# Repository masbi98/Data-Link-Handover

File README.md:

# Data-Link-Handover
a repository for handover the data link work that was done in my On-Job-Training with Gamuda Technologies.

# ExpressLRS to ArduPilot SITL Real-Time MAVLink Bridge

An ultra-low-latency hardware-in-the-loop (HIL) telemetry bridge developed during On-Job-Training with Gamuda Technologies. This repository provides the pipeline that captures native MAVLink RC override packets from an ExpressLRS (ELRS) receiver and injects them directly into ArduPilot Software-In-The-Loop (SITL) simulations via Mission Planner.

---

## 📌 Project Overview and Architecture

---

## 🛠️ Hardware & Software Stack

- **Transmitter:** Radiomaster T8L
- **Protocol:** ExpressLRS (2.4GHz) configured for MAVLink telemetry output
- **Interface:** FTDI USB-to-UART Serial Converter (`COM6`[or designated com port] `460800` baud)
- **Runtime / Libraries:** Python 3.10+, `pymavlink`
- **Ground Control & Simulation:** Mission Planner, ArduPilot SITL (Multirotor model)

---

## ⚡ Quick Start Guide

### 1. Prerequisites & Installation

Clone the repository and install dependencies:

```bash
git clone [https://github.com/masbi98/Data-Link-Handover.git]
cd Data-Link-Handover
pip install -r requirements.txt
```

### 2. Configure Mission Planner SITL

* Open Mission Planner
* Go to Simulation, choose Multirotor, and select Model. Allow the simulation to fuilly initialize.
* Open the developer utilities by pressing `Ctrl + F`, then click Mavlink.
* Configure the first row of the bridge table:
	- **Type:** `TCP`
	- **Direction:** `Inbound`
	- **Port:** `14556`
	- **Host/Baud:** mirror 14556
	- **Write:** [X] (Checked - critical for pass-through commands)
* Click Go (status much change to Started).

### 3. ArduPilot Parameter tweaks

To prevent false disarms during ground testing or packet jitters:

- Navigate to Config -> Full Parameters List.
- Set `FS_THR_Enable` to `0` (Disables RC throttle failsafe disarm during testing).
- Click Write params.

### 4. Run the Injection Script

Connect your receiver via FTDI and run (Assuming your working directory is already inside this repository):

```bash
python src/sitl_injector.py
```

### 5. Arm & Fly

* Switch to Mission Planner's Flight Data view.
* In the bottom-left **Actions** tab, set the flight mode to **Stabilize** and click **Set Mode**.
* Arm via sticks (Throttle down + Yaw right for 3s) or right-click the map -> **Arm/Disarm** -> **Force Arm**.
* Throttle up on your physical transmitter to control the virtual aircraft.

---

## 🦾 Troubleshooting Reference (System Failures Handled)

* Failed Connection/socket crashes (only one usage of socket address):
	- Causes: Background task ghosting on port `14555` or unclosed TCP relays.
	- Fixes: We routed standard connection ports exclusively onto unused port `14556`. When issues persist, kill tasks by hitting `Ctrl + C` and reboot Mission Planner to refresh system socket configurations.
* SITL parameter collection failures (No Heartbeat received):
	- Causes: Bridge logic crashing due to trying to map standard downloads inside Mission Planner.
	- Fixes: Never touch the main Mission Planer Connect button! Start SITL and connect directly using the internal bridge routing to communicate natively via GCS authentication (source_system=255).
* Uncontrolled random disarming:
	- Causes: Safety timeout failsafes and telemetry drops.
	- Fixes: Disabled internal failsafes (`FS_THR_ENABLE` to `0`) and changed raw signal tracking to asynchronous event-based pass-through triggers. No artificial delays are used, creating immediate, non-blocking control feedback.

---

## 🛠️ Custom PCB Design

This repo includes a custom-designed Printed Circuit Board (PCB) to handle the hardware routing between the ExpressLRS receiver, the microcontroller, and the power delivery systems.\

* **EDA Software:** KICAD
* **Layer Count:** 4 Layer Impedance-controlled stackup
* **Key Features:**
	- Dedicated UART routing for 460,800 baud telemetry lines.
	- Clean power delivery/filtering for the 2.4GHz RF module.
	- Broken-out programming header for flight controller firmware flashing.
* **Manufacturing:** The Zip file that is in the /hardware folder is used, and sent to JLCPCB. file name "Datalink Transceiver PCB files.zip"

---

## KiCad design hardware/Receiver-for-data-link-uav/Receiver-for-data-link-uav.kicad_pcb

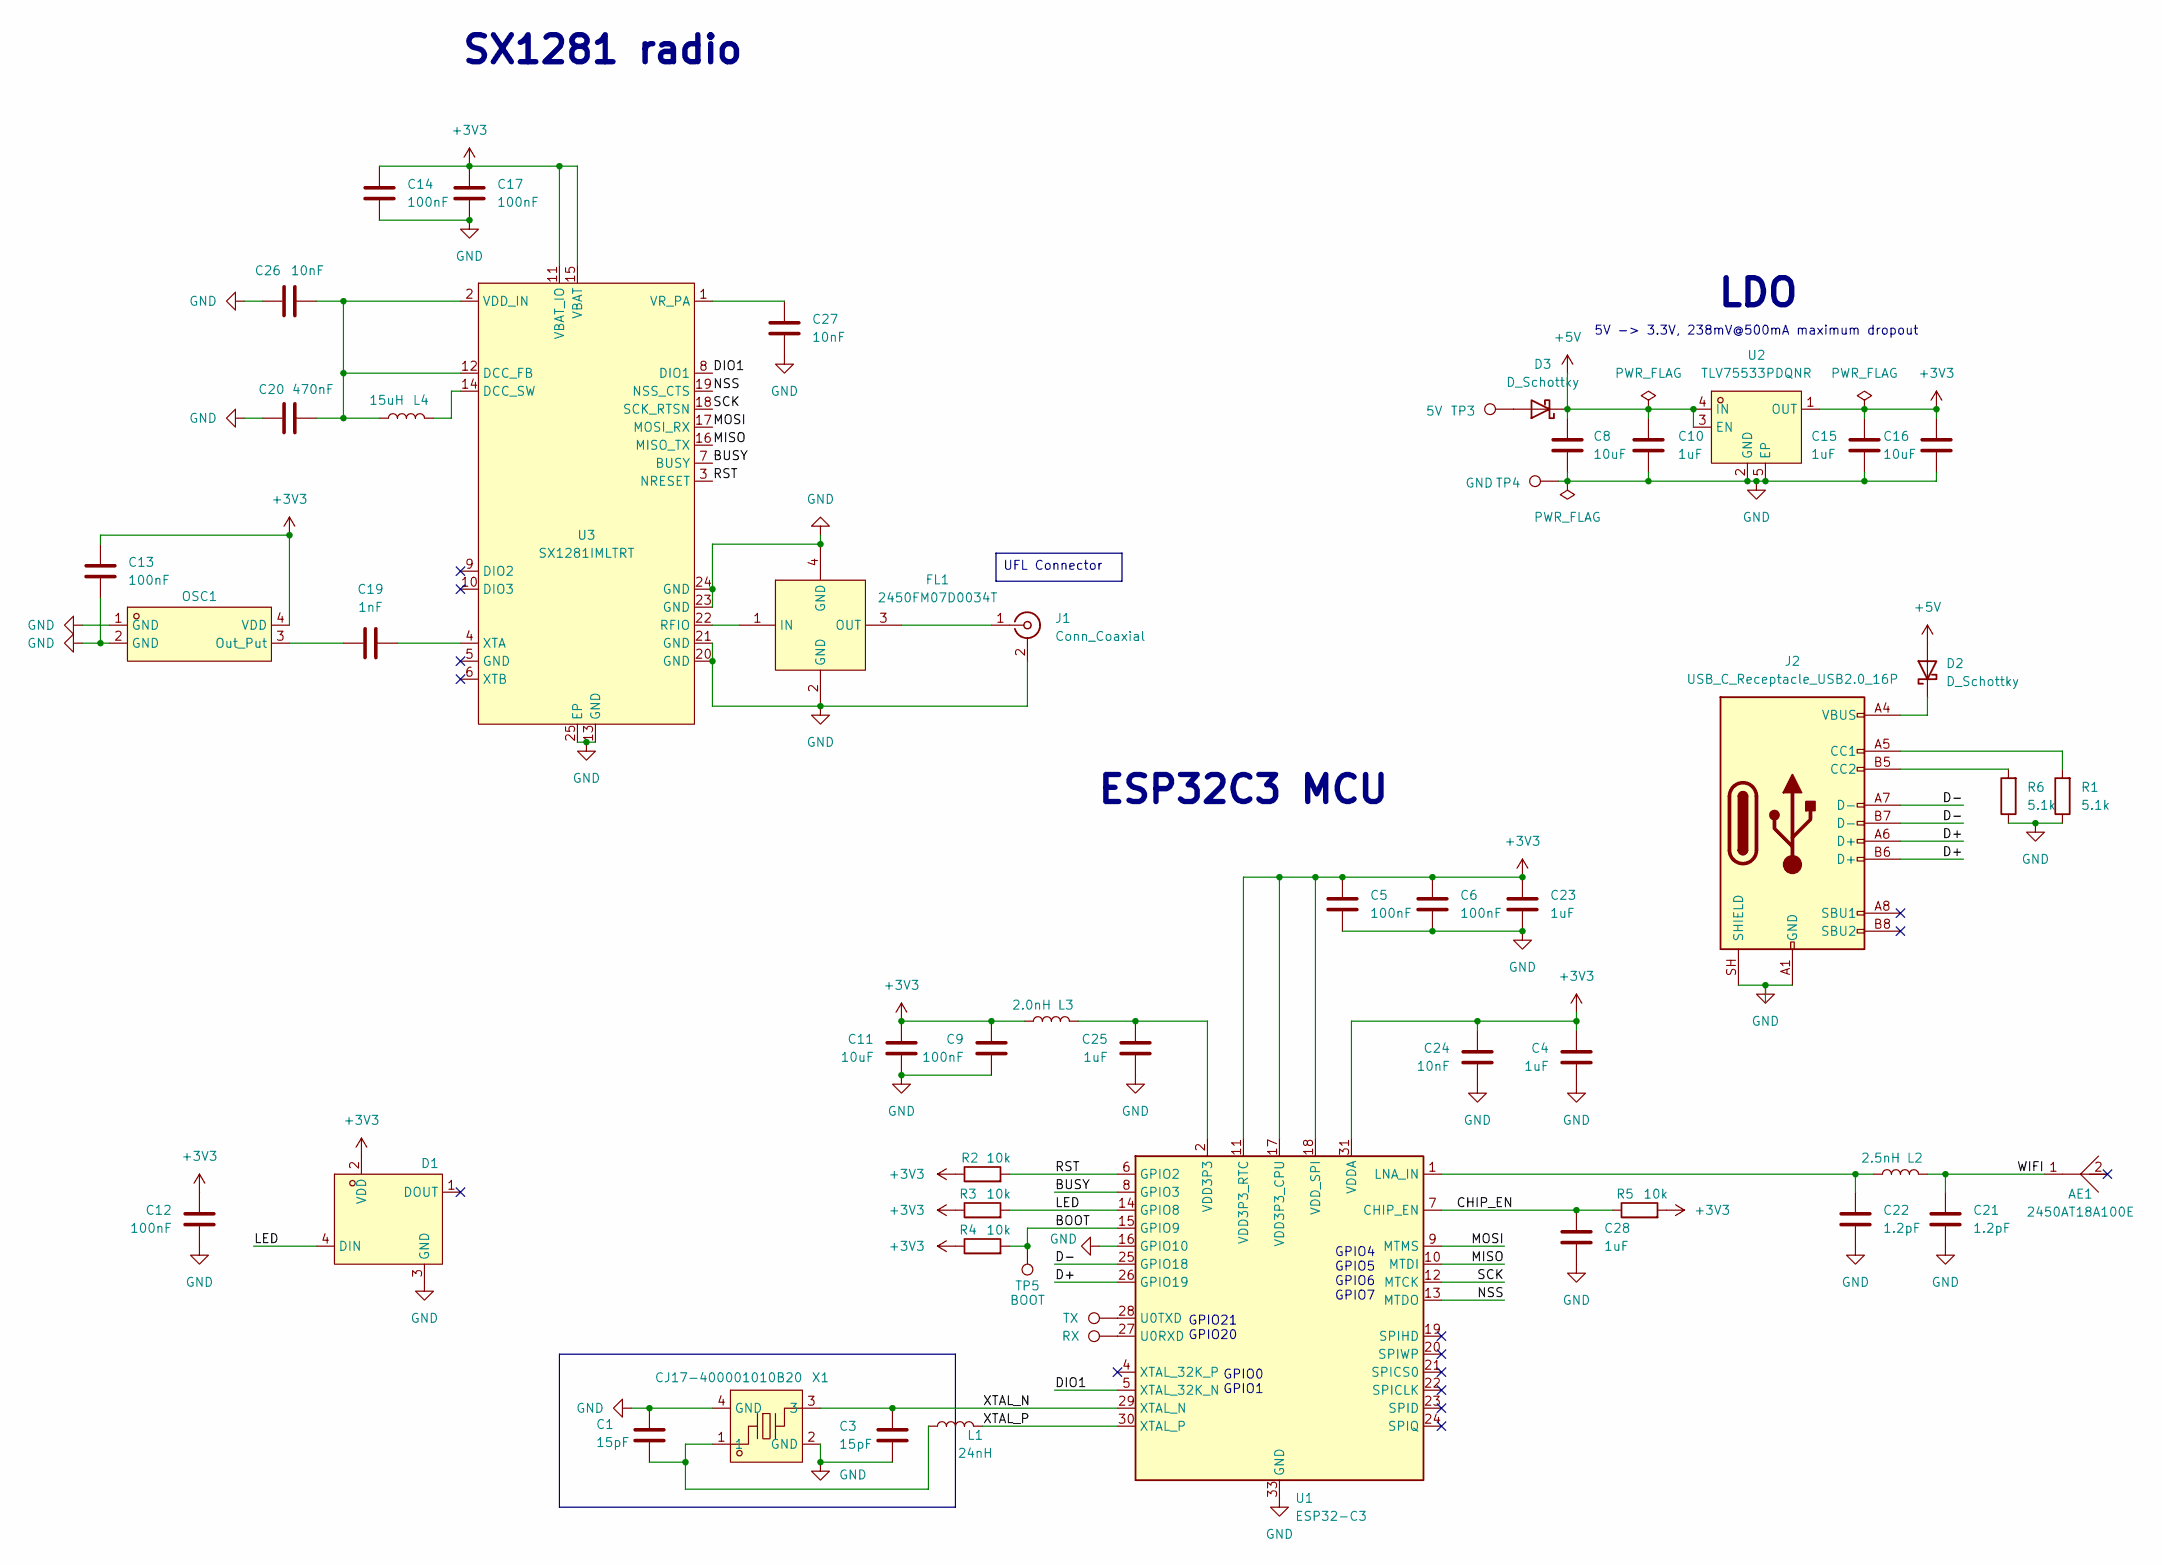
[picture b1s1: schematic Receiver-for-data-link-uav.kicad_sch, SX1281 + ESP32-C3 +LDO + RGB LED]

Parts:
AE1: 2450AT18A100E; ANT-SMD_L3.2-W1.6; LCSC Part C89334
C1, C3: 15pF; C_0201_0603Metric; LCSC C85891
C4, C10, C15, C23, C25, C28: 1uF; C_0201_0603Metric; LCSC C76935
C5, C6, C9, C12, C13, C14, C17: 100nF; C_0201_0603Metric; LCSC C76939
C8, C16: 10uF; C_0402_1005Metric; LCSC C15525
C11: 10uF; C_0402_1005Metric; LCSC C76991
C19: 1nF; C_0201_0603Metric; LCSC C66942
C20: 470nF; C_0201_0603Metric; LCSC C85926
C21, C22: 1.2pF; C_0201_0603Metric; LCSC C85895
C24, C26, C27: 10nF; C_0201_0603Metric; LCSC C2168164
D1: XL-1010RGBC-WS2812B; LED-SMD_4P-L1.0-W1.0-TL_XL-1010RGBC-WS2812B; LCSC Part C5349953
D2, D3: D_Schottky; D_SOD-123
FL1: 2450FM07D0034T; FILTER-SMD_4P-L1.0-W0.5-L; MPN 2450FM07D0034T; LCSC Part C2651081
J1: Conn_Coaxial; U.FL_Hirose_U.FL-R-SMT-1_Vertical; LCSC C88374
J2: USB_C_Receptacle_USB2.0_16P; USB_C_Receptacle_HRO_TYPE-C-31-M-12
L1: 24nH; L_0201_0603Metric; LCSC C206441
L2: 2.5nH; L_0201_0603Metric; LCSC C206435
L3: 2.0nH; L_0201_0603Metric; LCSC C86125
L4: 15uH; L_0805_2012Metric
OSC1: OW7EL89CENUNFAYLC-52M; OSC-SMD_4P-L2.0-W1.6-BL_TXC_7Z; LCSC Part C22434896
R1, R6: 5.1k; R_0402_1005Metric
R2, R3, R4, R5: 10k; R_0201_0603Metric; LCSC C106225
TP1: RX; SolderPad_1.2x2.0mm
TP2: TX; SolderPad_1.2x2.0mm
TP3: 5V; SolderPad_1.2x2.0mm
TP4: GND; SolderPad_1.2x2.0mm
TP5: BOOT; SolderPad_1.2x2.0mm
U1: ESP32-C3; QFN-32-1EP_5x5mm_P0.5mm_EP3.7x3.7mm
U2: TLV75533PDQNR; X2SON-4_L1.0-W1.0-P0.65-TL-EP; LCSC Part C2861882
U3: SX1281IMLTRT; QFN-24_L4.0-W4.0-P0.50-TL-EP2.6; LCSC Part C2151551
X1: CJ17-400001010B20; CRYSTAL-SMD_4P-L1.6-W1.2-BL; LCSC Part C2875272

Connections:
+3V3: C4.1, C5.1, C6.1, C9.1, C11.1, C12.1, C13.1, C14.1, C15.1, C16.1, C17.1, C23.1, C24.1, D1.2 (VDD), L3.2, OSC1.4 (VDD), R2.1, R3.1, R4.1, R5.2, U1.11 (VDD3P3_RTC), U1.17 (VDD3P3_CPU), U1.18 (VDD_SPI), U1.31 (VDDA), U1.32 (VDDA), U2.1 (OUT), U3.11 (VBAT_IO), U3.15 (VBAT)
+5V: C8.1, C10.1, D2.2 (A), D3.1 (K), U2.3 (EN), U2.4 (IN)
/BOOT: R4.2, TP5.1 (1_1), U1.15 (GPIO9)
/BUSY: U1.8 (GPIO3), U3.7 (BUSY)
/CHIP_EN: C28.1, R5.1, U1.7 (CHIP_EN)
/D+: J2.A6 (D+), J2.B6 (D+), U1.26 (GPIO19)
/D-: J2.A7 (D-), J2.B7 (D-), U1.25 (GPIO18)
/DIO1: U1.5 (XTAL_32K_N), U3.8 (DIO1)
/LED: D1.4 (DIN), R3.2, U1.14 (GPIO8)
/MISO: U1.10 (MTDI), U3.16 (MISO_TX)
/MOSI: U1.9 (MTMS), U3.17 (MOSI_RX)
/NSS: U1.13 (MTDO), U3.19 (NSS_CTS)
/RST: R2.2, U1.6 (GPIO2), U3.3 (NRESET)
/SCK: U1.12 (MTCK), U3.18 (SCK_RTSN)
/WIFI: AE1.1, C21.1, L2.1
/XTAL_N: C3.1, U1.29 (XTAL_N), X1.3
/XTAL_P: L1.2, U1.30 (XTAL_P)
GND: C1.2, C3.2, C4.2, C5.2, C6.2, C8.2, C9.2, C10.2, C11.2, C12.2, C13.2, C14.2, C15.2, C16.2, C17.2, C20.1, C21.2, C22.2, C23.2, C24.2, C25.2, C26.1, C27.2, C28.2, D1.3 (GND), FL1.2 (GND), FL1.4 (GND), J1.2 (Ext), J2.A1 (GND), J2.A12 (GND), J2.B1 (GND), J2.B12 (GND), J2.SH (SHIELD), OSC1.1 (GND), OSC1.2 (GND), R1.1, R6.1, TP4.1 (1_1), U1.16 (GPIO10), U1.33 (GND), U2.2 (GND), U2.5 (EP), U3.13 (GND), U3.20 (GND), U3.21 (GND), U3.23 (GND), U3.24 (GND), U3.25 (EP), X1.2 (GND), X1.4 (GND)
unnamed: C1.1, L1.1, X1.1
unnamed: C25.1, L3.1, U1.2 (VDD3P3), U1.3 (VDD3P3)
unnamed: D2.1 (K), J2.A4 (VBUS), J2.A9 (VBUS), J2.B4 (VBUS), J2.B9 (VBUS)
unnamed: D3.2 (A), TP3.1 (1_1)
unnamed: FL1.1 (IN), U3.22 (RFIO)
unnamed: FL1.3 (OUT), J1.1 (In)
unnamed: J2.A5 (CC1), R1.2
unnamed: J2.B5 (CC2), R6.2
unnamed: C19.1, OSC1.3 (Out_Put)
unnamed: C22.1, L2.2, U1.1 (LNA_IN)
unnamed: TP1.1 (1_1), U1.27 (U0RXD)
unnamed: TP2.1 (1_1), U1.28 (U0TXD)
unnamed: C20.2, C26.2, L4.1, U3.2 (VDD_IN), U3.12 (DCC_FB)
unnamed: L4.2, U3.14 (DCC_SW)
unnamed: C27.1, U3.1 (VR_PA)
unnamed: C19.2, U3.4 (XTA)

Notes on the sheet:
LDO
GPIO21 GPIO20
SX1281 radio
GPIO0 GPIO1
5V -> 3.3V, 238mV@500mA maximum dropout
GPIO4 GPIO5 GPIO6 GPIO7
ESP32C3 MCU
UFL Connector

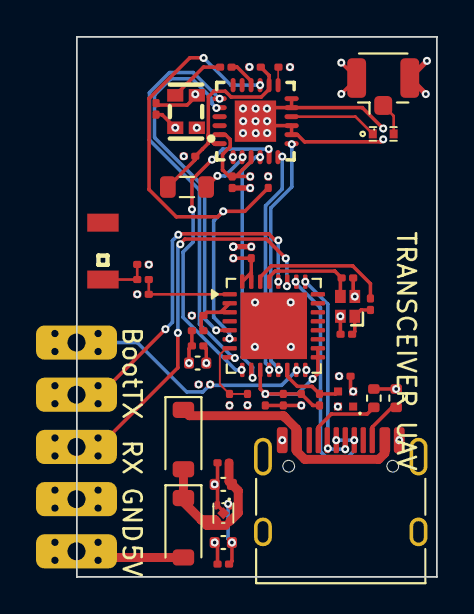
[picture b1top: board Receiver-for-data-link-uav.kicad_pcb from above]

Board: 4 copper layers, 20.0 x 30.0 mm, 52 parts (0 on the bottom side), 34 nets.
